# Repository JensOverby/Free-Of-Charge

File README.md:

# F-Of-C

## development has moved to this site: [VECTORWAVE](https://github.com/nordstream3/FOC)

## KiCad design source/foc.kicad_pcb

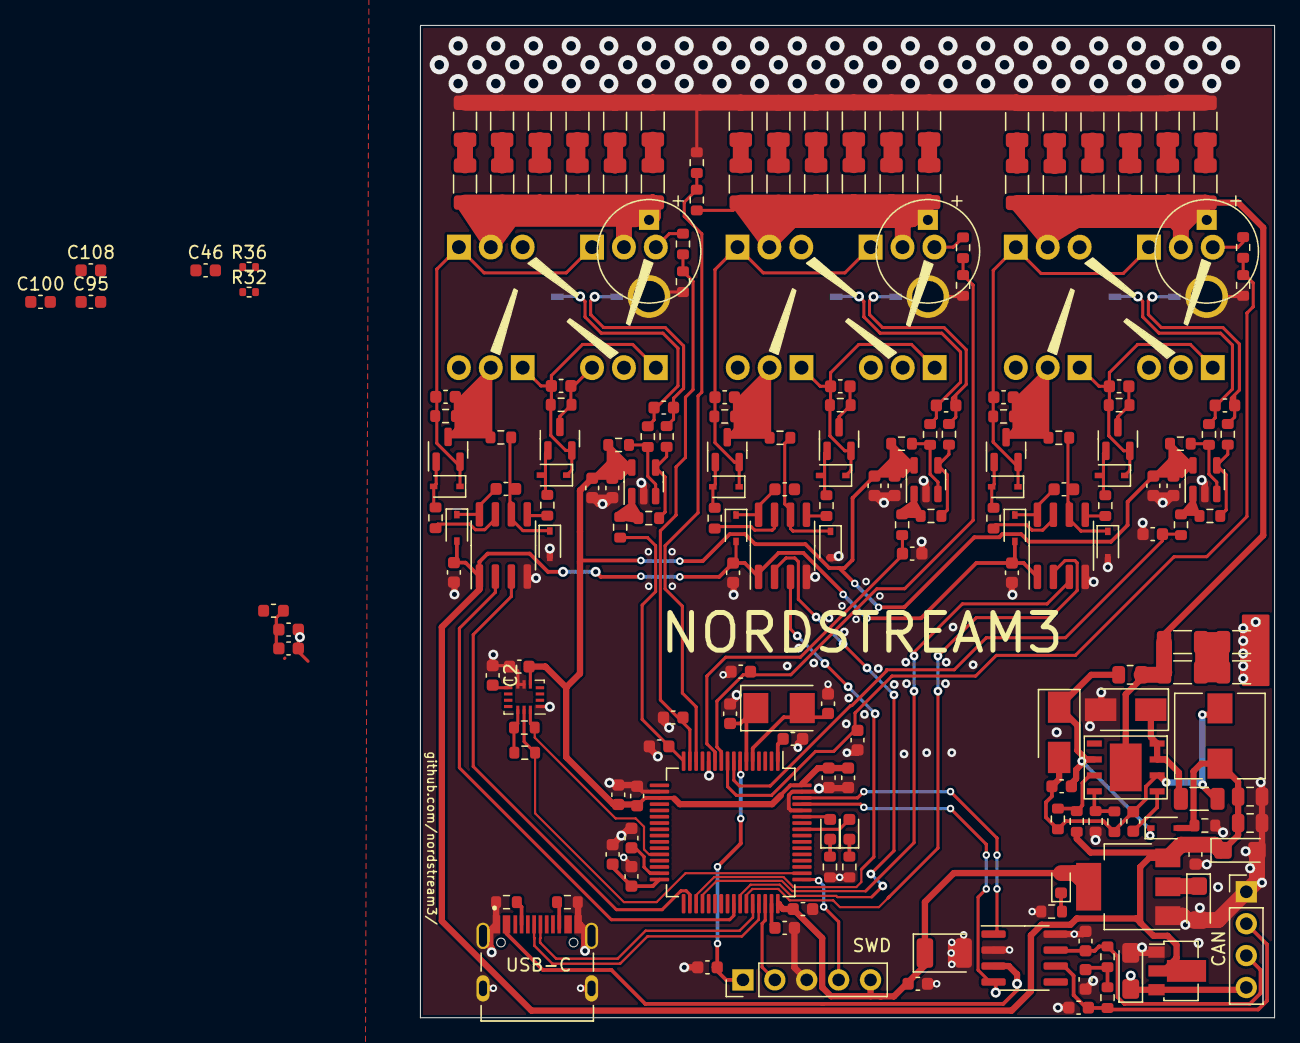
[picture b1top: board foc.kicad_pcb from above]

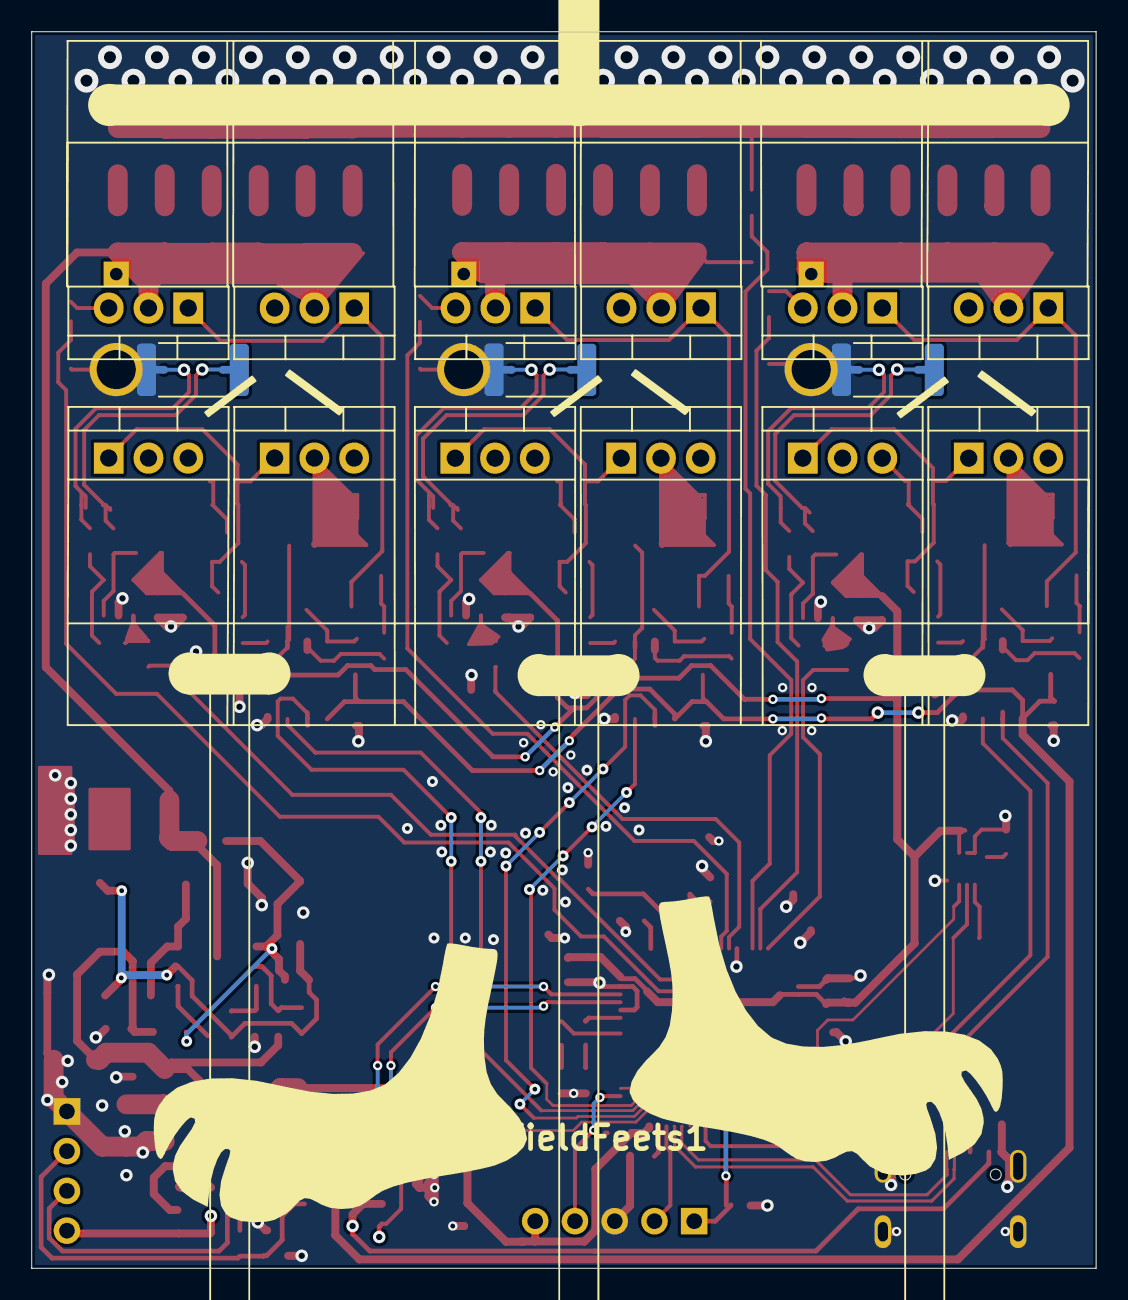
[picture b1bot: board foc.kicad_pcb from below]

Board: 2 copper layers, 68.0 x 79.0 mm, 224 parts (22 on the bottom side), 114 nets.

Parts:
C1, C2, C5, C8, C19, C25, C44, C63, C83, C84, C85, C93, C94, C95, C97, C100, C101, C103: 100n; C_0603_1608Metric
C3, C4, C7, C17, C18, C20, C24, C43, C46, C64, C89, C90, C91, C92, C104, C105, C106, C108: 2.2u; C_0603_1608Metric
C6: 100u; CP_EIA-3528-21_Kemet-B
C9, C10, C11, C12: 10u@50V; C_1206_3216Metric
C21, C22: 22u; C_0805_2012Metric
C23, C107: 10u; CP_EIA-3216-10_Kemet-I
C26, C45, C65: 1n; C_0603_1608Metric
C27, C28, C47, C48, C66, C67: 2.2nF; C_0603_1608Metric
C29, C49, C68, C86, C87: 100p; C_0603_1608Metric
C30, C31, C32, C33, C34, C35, C36, C37, C38, C39, C40, C41, C50, C51, C52, C53, C54, C55, C56, C57, C58, C59, C60, C61, C69, C70, C71, C72, C73, C74, C75, C76, C77, C78, C79, C80: 10u @ 50V; C_1206_3216Metric
C42, C62, C81: 470u 80V; CP_Radial_D8.0mm_P5.00mm
C82: 4.7n; C_0603_1608Metric
C88: 10u; CP_EIA-3216-10_Kemet-I_Pad1.58x1.35mm_HandSolder
C96: 1u; C_0603_1608Metric
C98: 10n; C_0603_1608Metric
C99, C102: 15p; C_0603_1608Metric
CYA0650-68UH1: 68uH; L_6.6x7.2_H5.0_CYA0650_68UH
D1, D2, D3, D4, D5, D7, D8, D10, D11, D12, D13, D14, D15: 1N4148WS; D_SOD-323
D6, D9: SS210; D_SMA
D16: RED; LED_0603_1608Metric
D17: GRN; LED_0603_1608Metric
D18: BLU; LED_0603_1608Metric
FieldFeets1: R; field
J1: Conn_01x04_Male; PinHeader_1x04_P2.54mm_Vertical
J2: TYPE-C-31-M-12; HRO_TYPE-C-31-M-12
L1: 30n; L_0603_1608Metric
NT1, NT2, NT3, NT4, NT5, NT6: NetTie_2; NetTie-2_SMD_Pad0.5mm
P1: SWD; PinHeader_1x05_P2.54mm_Vertical
Q1, Q2, Q7, Q8, Q13, Q14: MMBT5401; SOT-23
Q3: NCEP60T20; TO-220-3_Vertical
Q4, Q5, Q6, Q9, Q10, Q11, Q12, Q15, Q16, Q17, Q18: CSD19536KCS; TO-220-3_Vertical
R1, R2, R28, R29, R40, R41, R50, R51: 1k; R_0603_1608Metric
R3, R6, R8, R12: 56k @ 75V; R_0603_1608Metric
R4, R7, R9, R13, R20: 2k; R_0603_1608Metric
R5, R10, R15: 2R; R_0603_1608Metric
R11: 82k @ 150V; R_0805_2012Metric
R14, R18: 1k8; R_0603_1608Metric
R16, R17: 56k; R_0603_1608Metric
R19: 0.1R; R_1206_3216Metric
R21, R24, R31, R35, R43, R46: 30k; R_0603_1608Metric
R22, R23, R33, R34, R44, R45: 4.7R; R_0603_1608Metric
R25, R37, R47: 62k; R_0603_1608Metric
R26, R27, R38, R39, R48, R49: 4.7k @ 75v; R_0603_1608Metric
R30, R42, R52: ASR-M-3-0.25F 0.25mR; R_2512_6332Metric
R32: NTC 10k; R_0402_1005Metric
R36: 10k; R_0402_1005Metric
R53, R54: 100Ω; R_0603_1608Metric
R55, R56: 5.1k; R_0603_1608Metric
R57, R58, R59: 20k; R_0603_1608Metric
U1: BMI160; Bosch_LGA-14_3x2.5mm_P0.5mm
U2, U3, U4: IRS21867S; SOIC-8_3.9x4.9mm_P1.27mm
U5: TX4130L/PW2902; TX4130L_ESOP-8
U6: MS8311; SOT-23-5_MS8311
U7, U8: MS8311; TSOT-23-5
U9: TJA1050T/CM,118; SOIC-8_3.9x4.9mm_P1.27mm
U10: HT7550; SOT-89-3
U11: STM32F405RGT6; LQFP-64_10x10mm_P0.5mm
U12: AMS1117-3.3; SOT-223-3_TabPin2
Y1: 8MHz Crystal Resonator, X50328MSB2GI; Crystal_SMD_5032-2Pin_5.0x3.2mm

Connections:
+5V: C88.1, J1.4, J2.A4B9 (VBUS), J2.B4A9 (VBUS), U9.3 (VCC), U10.3 (VO)
+12V: C3.1, C7.1, C17.1, C21.1, C22.1, C23.1, C103.2, CYA0650-68UH1.2, D1.2 (A), D3.2 (A), D5.2 (A), D7.2 (A), R16.1, R20.2, U2.1 (VCC), U3.1 (VCC), U4.1 (VCC), U10.2 (VI), U12.3 (VI)
/driver/H1: U2.2 (HIN), U11.41 (PA8)
/driver/H2: U3.2 (HIN), U11.42 (PA9(OTG_FS_VBUS))
/driver/H3: U4.2 (HIN), U11.43 (PA10)
/driver/HO1: R22.1, U2.7 (HO)
/driver/HO2: R33.1, U3.7 (HO)
/driver/HO3: R44.1, U4.7 (HO)
/driver/HS1: C27.2, Q1.3 (C), Q3.3 (S), Q4.2 (D), Q5.3 (S), Q6.2 (D), R3.2, R5.2, R26.1
/driver/HS2: C47.2, Q7.3 (C), Q9.3 (S), Q10.2 (D), Q11.3 (S), Q12.2 (D), R8.2, R10.2, R38.1
/driver/HS3: C66.2, Q13.3 (C), Q15.3 (S), Q16.2 (D), Q17.3 (S), Q18.2 (D), R12.2, R15.2, R48.1
/driver/L1: U2.3 (LIN), U11.34 (PB13(OTG_HS_VBUS))
/driver/L2: U3.3 (LIN), U11.35 (PB14)
/driver/L3: U4.3 (LIN), U11.36 (PB15)
/driver/LO1: R23.1, U2.5 (LO)
/driver/LO2: R34.1, U3.5 (LO)
/driver/LO3: R45.1, U4.5 (LO)
/driver/SENS_1: C83.1, R3.1, R4.1, U11.15 (PA1(ADC123_IN1))
/driver/SENS_2: C84.1, R8.1, R9.1, U11.10 (PC2(ADC123_IN12))
/driver/SENS_3: C85.1, R12.1, R13.1, U11.9 (PC1(ADC123_IN11))
/driver/SENS_SUPPLY: R6.1, R7.1, U11.14 (PA0(ADC123_IN0/WKUP))
/mcu/3.3VA: C96.1, C98.1, L1.2, U11.13 (VDDA)
/mcu/ADC_TEMP: C46.2, R32.1, R36.2, U11.17 (PA3(ADC123_IN3))
/mcu/CAN_RX: U9.4 (RXD), U11.61 (PB8)
/mcu/CAN_TX: U9.1 (TXD), U11.62 (PB9)
/mcu/CURRENT_1: C26.2, R21.2, U11.16 (PA2(ADC123_IN2))
/mcu/CURRENT_2: C45.2, R31.2, U11.11 (PC3(ADC123_IN13))
/mcu/CURRENT_3: C65.2, R43.2, U11.8 (PC0(ADC123_IN10))
/mcu/LED_GREEN: D17.2 (A), U11.57 (PB5)
/mcu/LED_RED: D16.2 (A), U11.59 (PB7)
/mcu/NRST: C93.2, P1.1, U11.7 (NRST)
/mcu/PA15: R2.2, U1.13 (SCX), U11.50 (PA15(JTDI))
/mcu/PB2: R1.1, U1.14 (SDX), U11.28 (PB2-BOOT1)
/mcu/PH0: C99.1, U11.6 (PH1-OSC_OUT), Y1.1
/mcu/PH1: C102.1, U11.5 (PH0-OSC_IN), Y1.2
/mcu/SWCLK: P1.4, U11.49 (PA14(JTCK-SWCLK))
/mcu/SWDIO: P1.2, U11.46 (PA13(JTMS-SWDIO))
/mcu/USB_D+: J2.A6 (DP1), J2.B6 (DP2), U11.45 (PA12)
/mcu/USB_D-: J2.A7 (DN1), J2.B7 (DN2), U11.44 (PA11)
GND: C1.1, C2.1, C3.2, C4.2, C6.2, C7.2, C10.1, C12.2, C17.2, C21.2, C22.2, C23.2, C24.1, C25.1, C26.1, C31.1, C33.1, C35.1, C37.1, C39.1, C41.1, C42.2, C43.1, C44.1, C45.1, C46.1, C51.1, C53.1, C55.1, C57.1, C59.1, C61.1, C62.2, C63.2, C64.2, C65.1, C70.1, C72.1, C74.1, C76.1, C78.1, C80.1, C81.2, C82.2, C83.2, C84.2, C85.2, C86.2, C87.2, C88.2, C89.2, C90.2, C91.2, C92.2, C93.1, C94.2, C95.2, C96.2, C97.2, C98.2, C99.2, C100.2, C101.2, C102.2, C103.1, C104.1, C105.1, C106.1, C107.2, C108.1, D2.2 (A), D4.2 (A), D8.2 (A), D9.2 (A), J1.1, J2.A1B12 (GND), J2.B1A12 (GND), J2.S1 (SHIELD), J2.S2 (SHIELD), J2.S3 (SHIELD), J2.S4 (SHIELD), NT2.2, NT4.2, NT6.2, P1.3, R4.2, R7.2, R9.2, R13.2, R17.1, R20.1, R30.2, R36.1, R42.2, R52.2, R55.2, R56.2, R57.1, R58.1, R59.1, U1.1 (SDO), U1.6 (GNDIO), U1.7 (GND), U2.4 (COM), U3.4 (COM), U4.4 (COM), U6.2 (V-), U7.2 (V-), U8.2 (V-), U9.2 (GND), U9.8 (S), U10.1 (GND), U11.12 (VSSA), U11.18 (VSS), U11.60 (BOOT0(VPP)), U11.63 (VSS), U12.1 (GND)
unnamed: C5.1, D1.1 (K), U2.8 (VB)
unnamed: C5.2, D2.1 (K), R5.1, U2.6 (VS)
unnamed: C8.1, D3.1 (K), U3.8 (VB)
unnamed: C8.2, D4.1 (K), R10.1, U3.6 (VS)
unnamed: C9.1, C10.2
unnamed: C11.2, C12.1
unnamed: C18.1, C20.1, CYA0650-68UH1.1, D6.2 (A), R14.1, R18.1, R19.1, U5.6 (VSS)
unnamed: C18.2, D5.1 (K), D6.1 (K), R11.1, U5.2 (VDD)
unnamed: C19.1, D7.1 (K), U4.8 (VB)
unnamed: C19.2, D8.1 (K), R15.1, U4.6 (VS)
unnamed: C20.2, U5.5 (LDO)
unnamed: C27.1, D10.1 (K), Q1.2 (E), Q3.1 (G), Q5.1 (G), R26.2
unnamed: C28.1, D11.1 (K), Q2.2 (E), Q4.1 (G), Q6.1 (G), R27.2
unnamed: C28.2, NT1.2, Q2.3 (C), Q4.3 (S), Q6.3 (S), R27.1, R30.1
unnamed: C29.1, NT2.1, R29.1
unnamed: C29.2, NT1.1, R28.1
unnamed: C30.1, C31.2
unnamed: C32.1, C33.2
unnamed: C34.1, C35.2
unnamed: C36.1, C37.2
unnamed: C38.1, C39.2
unnamed: C40.1, C41.2
unnamed: C47.1, D12.1 (K), Q7.2 (E), Q9.1 (G), Q11.1 (G), R38.2
unnamed: C48.1, D13.1 (K), Q8.2 (E), Q10.1 (G), Q12.1 (G), R39.2
unnamed: C48.2, NT3.2, Q8.3 (C), Q10.3 (S), Q12.3 (S), R39.1, R42.1
unnamed: C49.1, NT4.1, R41.1
unnamed: C49.2, NT3.1, R40.1
unnamed: C50.1, C51.2
unnamed: C52.1, C53.2
unnamed: C54.1, C55.2
unnamed: C56.1, C57.2
unnamed: C58.1, C59.2
unnamed: C60.1, C61.2
unnamed: C66.1, D14.1 (K), Q13.2 (E), Q15.1 (G), Q17.1 (G), R48.2
unnamed: C67.1, D15.1 (K), Q14.2 (E), Q16.1 (G), Q18.1 (G), R49.2
unnamed: C67.2, NT5.2, Q14.3 (C), Q16.3 (S), Q18.3 (S), R49.1, R52.1
unnamed: C68.1, NT6.1, R51.1
unnamed: C68.2, NT5.1, R50.1
unnamed: C69.1, C70.2
unnamed: C71.1, C72.2
unnamed: C73.1, C74.2
unnamed: C75.1, C76.2
unnamed: C77.1, C78.2
unnamed: C79.1, C80.2
unnamed: C82.1, R53.1, R54.2
unnamed: C86.1, J1.3, R53.2, U9.7 (CANH)
unnamed: C87.1, J1.2, R54.1, U9.6 (CANL)
unnamed: C89.1, U11.47 (VCAP2)
unnamed: C90.1, U11.31 (VCAP1)
unnamed: D9.1 (K), R19.2, U5.7 (VSEN), U5.8 (VSEND)
unnamed: D10.2 (A), Q1.1 (B), R22.2
unnamed: D11.2 (A), Q2.1 (B), R23.2
unnamed: D12.2 (A), Q7.1 (B), R33.2
unnamed: D13.2 (A), Q8.1 (B), R34.2
unnamed: D14.2 (A), Q13.1 (B), R44.2
unnamed: D15.2 (A), Q14.1 (B), R45.2
unnamed: D16.1 (K), R57.2
unnamed: D17.1 (K), R58.2
unnamed: D18.1 (K), R59.2
unnamed: J2.A5 (CC1), R55.1
unnamed: J2.B5 (CC2), R56.1
unnamed: R14.2, R16.2, U5.3 (FB1)
unnamed: R17.2, R18.2, U5.4 (FB2)
unnamed: R21.1, R24.2, U6.1
unnamed: R24.1, R29.2, U6.4 (-)
unnamed: R25.1, R28.2, U6.3 (+)
unnamed: R31.1, R35.2, U7.1
unnamed: R35.1, R41.2, U7.4 (-)
unnamed: R37.1, R40.2, U7.3 (+)
unnamed: R43.1, R46.2, U8.1
unnamed: R46.1, R51.2, U8.4 (-)
unnamed: R47.1, R50.2, U8.3 (+)
VCC: C1.2, C2.2, C4.1, C6.1, C24.2, C25.2, C43.2, C44.2, C63.1, C64.1, C91.1, C92.1, C94.1, C95.1, C97.1, C100.1, C101.1, C104.2, C105.2, C106.2, C107.1, C108.2, D18.2 (A), L1.1, P1.5, R1.2, R2.1, R25.2, R32.2, R37.2, R47.2, U1.5 (VDDIO), U1.8 (VDD), U1.12 (CSB), U6.5 (V+), U7.5 (V+), U8.5 (V+), U11.1 (VBAT), U11.19 (VDD), U11.32 (VDD), U11.48 (VDD), U11.64 (VDD), U12.2 (VO)
V_IN: C9.2, C11.1, C30.2, C32.2, C34.2, C36.2, C38.2, C40.2, C42.1, C50.2, C52.2, C54.2, C56.2, C58.2, C60.2, C62.1, C69.2, C71.2, C73.2, C75.2, C77.2, C79.2, C81.1, Q3.2 (D), Q5.2 (D), Q9.2 (D), Q11.2 (D), Q15.2 (D), Q17.2 (D), R6.2, R11.2, U5.1 (VIN), U5.9 (VIN)

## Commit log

2023-03-19 Changes suggested by mxlemming, Elwin and hackey on Discord
    New power supplies and using other op-amps for current sense
2023-03-26 First attempt of layout
    It's a rats nest. Will have to remove some connections temporarily for the first prototype.
2023-03-26 First attempt of layout
2023-03-31 Most components now jlcpcb basic
